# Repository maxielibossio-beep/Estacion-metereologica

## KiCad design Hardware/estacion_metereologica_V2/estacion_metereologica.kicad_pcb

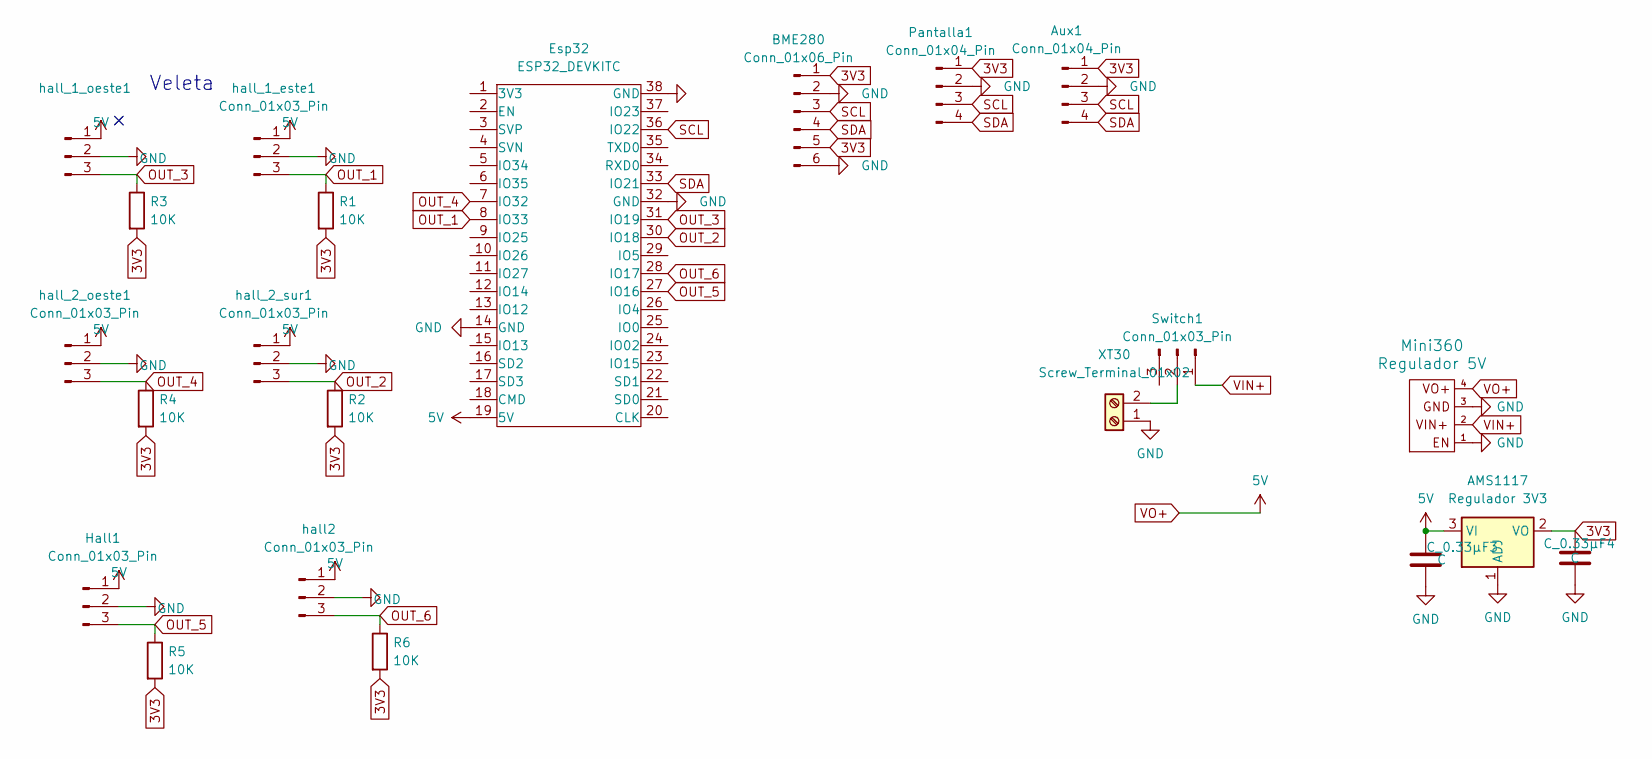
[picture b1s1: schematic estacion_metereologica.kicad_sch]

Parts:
AMS1117: Regulador 3V3; SOT-223-3_TabPin2
Aux1: Conn_01x04_Pin; JST_EH_B4B-EH-A_1x04_P2.50mm_Vertical
BME280: Conn_01x06_Pin; PinHeader_1x06_P2.54mm_Vertical
C_0.33µF3, C_0.33µF4: C; C_0805_2012Metric
Esp32: ESP32_DEVKITC; ESP32-DevKitC
Hall1: Conn_01x03_Pin; JST_XH_B3B-XH-A_1x03_P2.50mm_Vertical
Mini360: Regulador 5V; Mini360
Pantalla1: Conn_01x04_Pin; JST_EH_B4B-EH-A_1x04_P2.50mm_Vertical
R1, R2, R3, R4, R5, R6: 10K; R_0805_2012Metric_Pad1.20x1.40mm_HandSolder
Switch1: Conn_01x03_Pin; JST_PH_B3B-PH-K_1x03_P2.00mm_Vertical
XT30: Screw_Terminal_01x02; AMASS_XT30U-F_1x02_P5.0mm_Vertical
hall2: Conn_01x03_Pin; JST_XH_B3B-XH-A_1x03_P2.50mm_Vertical
hall_1_este1, hall_1_oeste1, hall_2_oeste1, hall_2_sur1: Conn_01x03_Pin; JST_XH_B3B-XH-A_1x03_P2.50mm_Vertical

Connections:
3V3: AMS1117.2 (VO), Aux1.1, BME280.1, BME280.5, C_0.33µF4.1, Pantalla1.1, R1.2, R2.2, R3.2, R4.2, R5.2, R6.2
GND: AMS1117.1 (ADJ), Aux1.2, BME280.2, BME280.6, C_0.33µF3.2, C_0.33µF4.2, Esp32.14 (GND), Esp32.32 (GND), Esp32.38 (GND), Hall1.2, Mini360.1, Mini360.3, Pantalla1.2, XT30.1, hall2.2, hall_1_este1.2, hall_1_oeste1.2, hall_2_oeste1.2, hall_2_sur1.2
unnamed: Switch1.2, XT30.2
OUT_1: Esp32.8 (IO33), R1.1, hall_1_este1.3
OUT_2: Esp32.30 (IO18), R2.1, hall_2_sur1.3
OUT_3: Esp32.31 (IO19), R3.1, hall_1_oeste1.3
OUT_4: Esp32.7 (IO32), R4.1, hall_2_oeste1.3
OUT_5: Esp32.27 (IO16), Hall1.3, R5.1
OUT_6: Esp32.28 (IO17), R6.1, hall2.3
SCL: Aux1.3, BME280.3, Esp32.36 (IO22), Pantalla1.3
SDA: Aux1.4, BME280.4, Esp32.33 (IO21), Pantalla1.4
VIN+: Mini360.2, Switch1.1
VO+: AMS1117.3 (VI), C_0.33µF3.1, Esp32.19 (5V), Hall1.1, Mini360.4, hall2.1, hall_1_este1.1, hall_1_oeste1.1, hall_2_oeste1.1, hall_2_sur1.1

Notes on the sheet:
Veleta

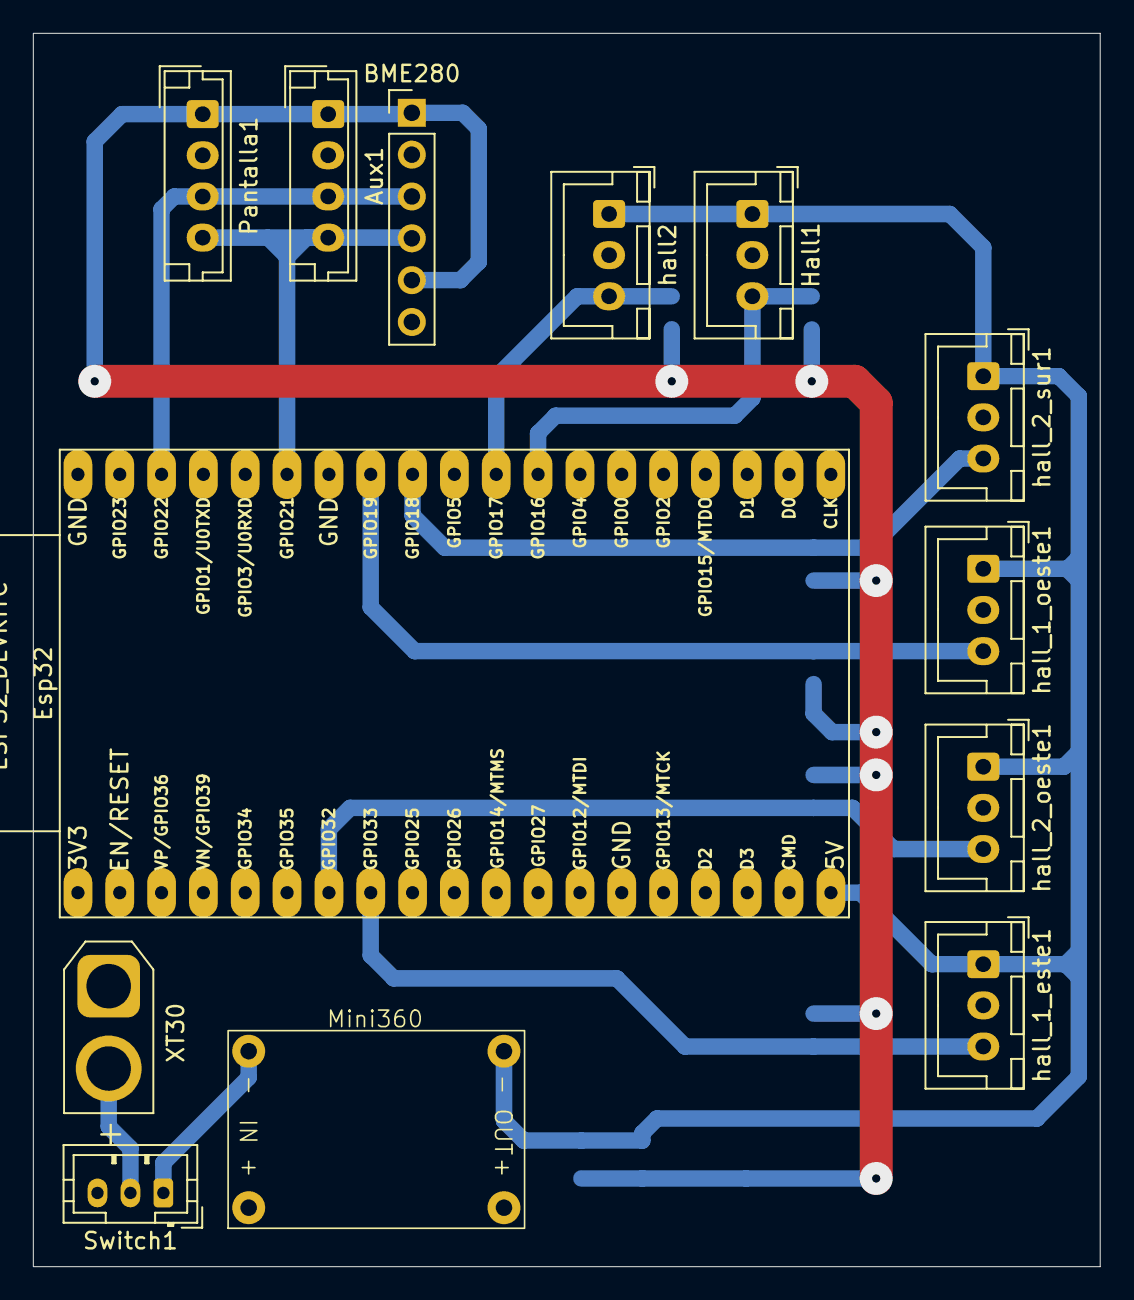
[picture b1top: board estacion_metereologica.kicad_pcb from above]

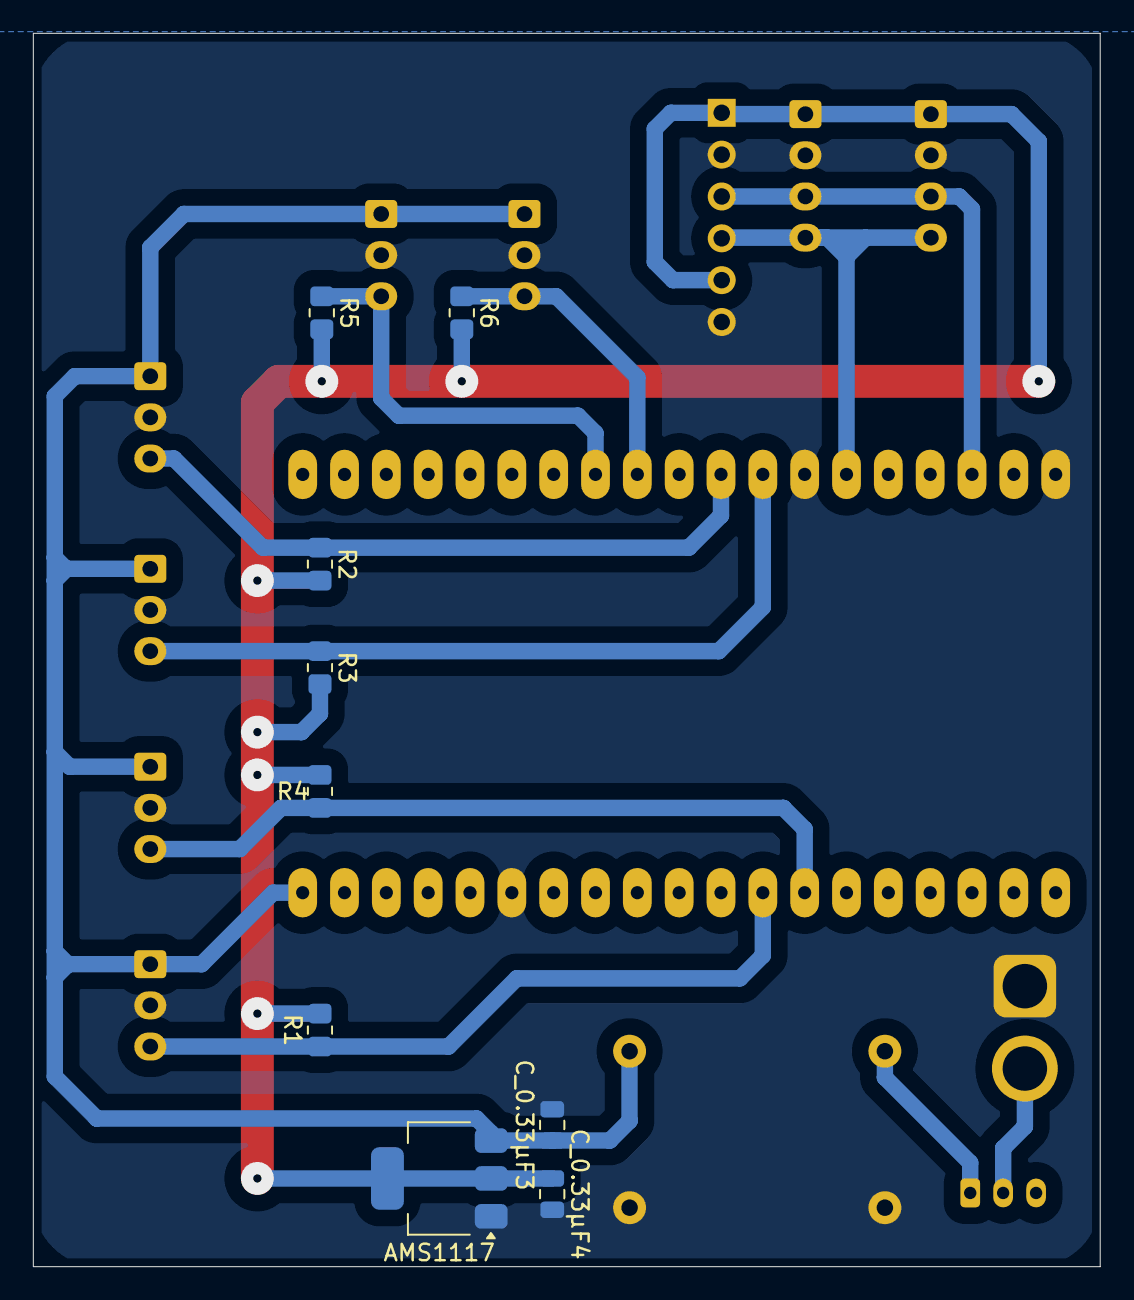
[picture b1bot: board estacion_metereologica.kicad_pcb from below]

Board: 2 copper layers, 64.8 x 74.9 mm, 22 parts (9 on the bottom side), 13 nets.

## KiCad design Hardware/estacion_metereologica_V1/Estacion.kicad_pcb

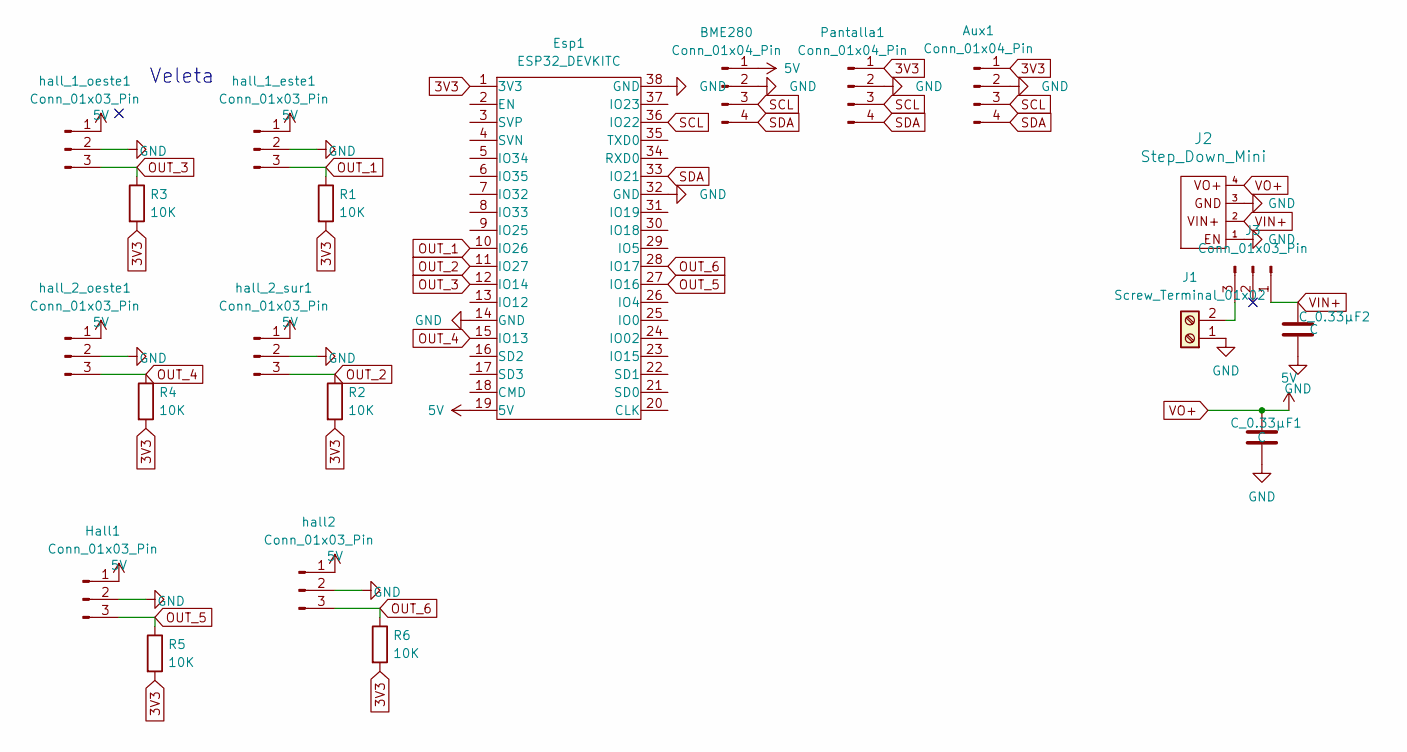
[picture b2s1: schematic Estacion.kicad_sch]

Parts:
Aux1: Conn_01x04_Pin; JST_PH_B4B-PH-K_1x04_P2.00mm_Vertical
BME280: Conn_01x04_Pin; JST_PH_B4B-PH-K_1x04_P2.00mm_Vertical
C_0.33µF1, C_0.33µF2: C; C_0805_2012Metric
Esp1: ESP32_DEVKITC; ESP32-DevKitC
Hall1: Conn_01x03_Pin; JST_PH_B3B-PH-K_1x03_P2.00mm_Vertical
J1: Screw_Terminal_01x02; AMASS_XT30U-F_1x02_P5.0mm_Vertical
J2: Step_Down_Mini; Mini360
J3: Conn_01x03_Pin; JST_PH_B3B-PH-K_1x03_P2.00mm_Vertical
Pantalla1: Conn_01x04_Pin; JST_PH_B4B-PH-K_1x04_P2.00mm_Vertical
R1, R2, R3, R4, R5, R6: 10K; R_0805_2012Metric_Pad1.20x1.40mm_HandSolder
hall2: Conn_01x03_Pin; JST_PH_B3B-PH-K_1x03_P2.00mm_Vertical
hall_1_este1, hall_1_oeste1, hall_2_oeste1, hall_2_sur1: Conn_01x03_Pin; JST_PH_B3B-PH-K_1x03_P2.00mm_Vertical

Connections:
3V3: Aux1.1, Esp1.1 (3V3), Pantalla1.1, R1.2, R2.2, R3.2, R4.2, R5.2, R6.2
GND: Aux1.2, BME280.2, C_0.33µF1.2, C_0.33µF2.2, Esp1.14 (GND), Esp1.32 (GND), Esp1.38 (GND), Hall1.2, J1.1, J2.1, J2.3, Pantalla1.2, hall2.2, hall_1_este1.2, hall_1_oeste1.2, hall_2_oeste1.2, hall_2_sur1.2
unnamed: J1.2, J3.3
OUT_1: Esp1.10 (IO26), R1.1, hall_1_este1.3
OUT_2: Esp1.11 (IO27), R2.1, hall_2_sur1.3
OUT_3: Esp1.12 (IO14), R3.1, hall_1_oeste1.3
OUT_4: Esp1.15 (IO13), R4.1, hall_2_oeste1.3
OUT_5: Esp1.27 (IO16), Hall1.3, R5.1
OUT_6: Esp1.28 (IO17), R6.1, hall2.3
SCL: Aux1.3, BME280.3, Esp1.36 (IO22), Pantalla1.3
SDA: Aux1.4, BME280.4, Esp1.33 (IO21), Pantalla1.4
VIN+: C_0.33µF2.1, J2.2, J3.1
VO+: BME280.1, C_0.33µF1.1, Esp1.19 (5V), Hall1.1, J2.4, hall2.1, hall_1_este1.1, hall_1_oeste1.1, hall_2_oeste1.1, hall_2_sur1.1

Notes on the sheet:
Veleta

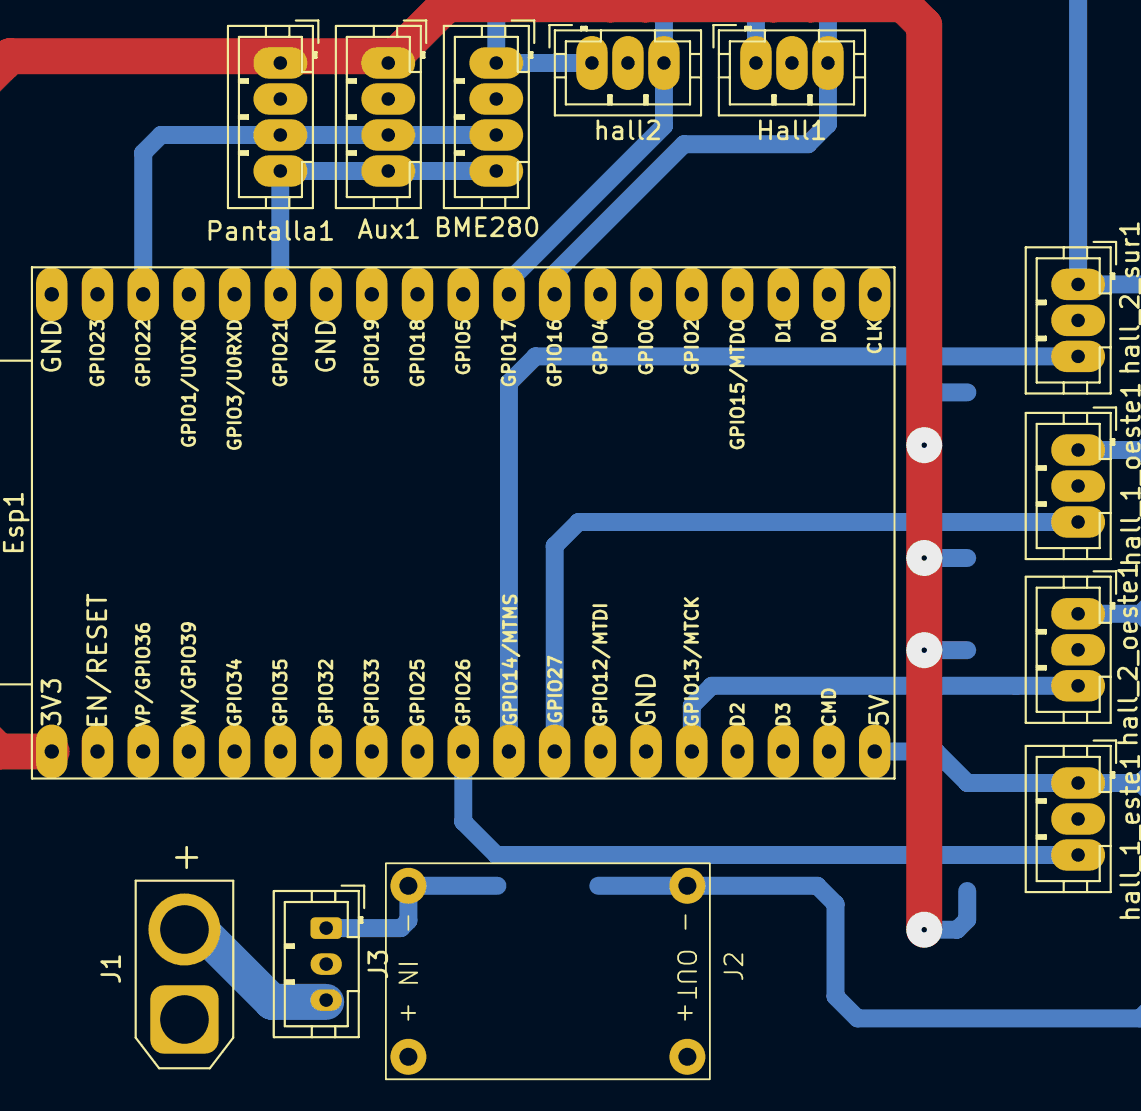
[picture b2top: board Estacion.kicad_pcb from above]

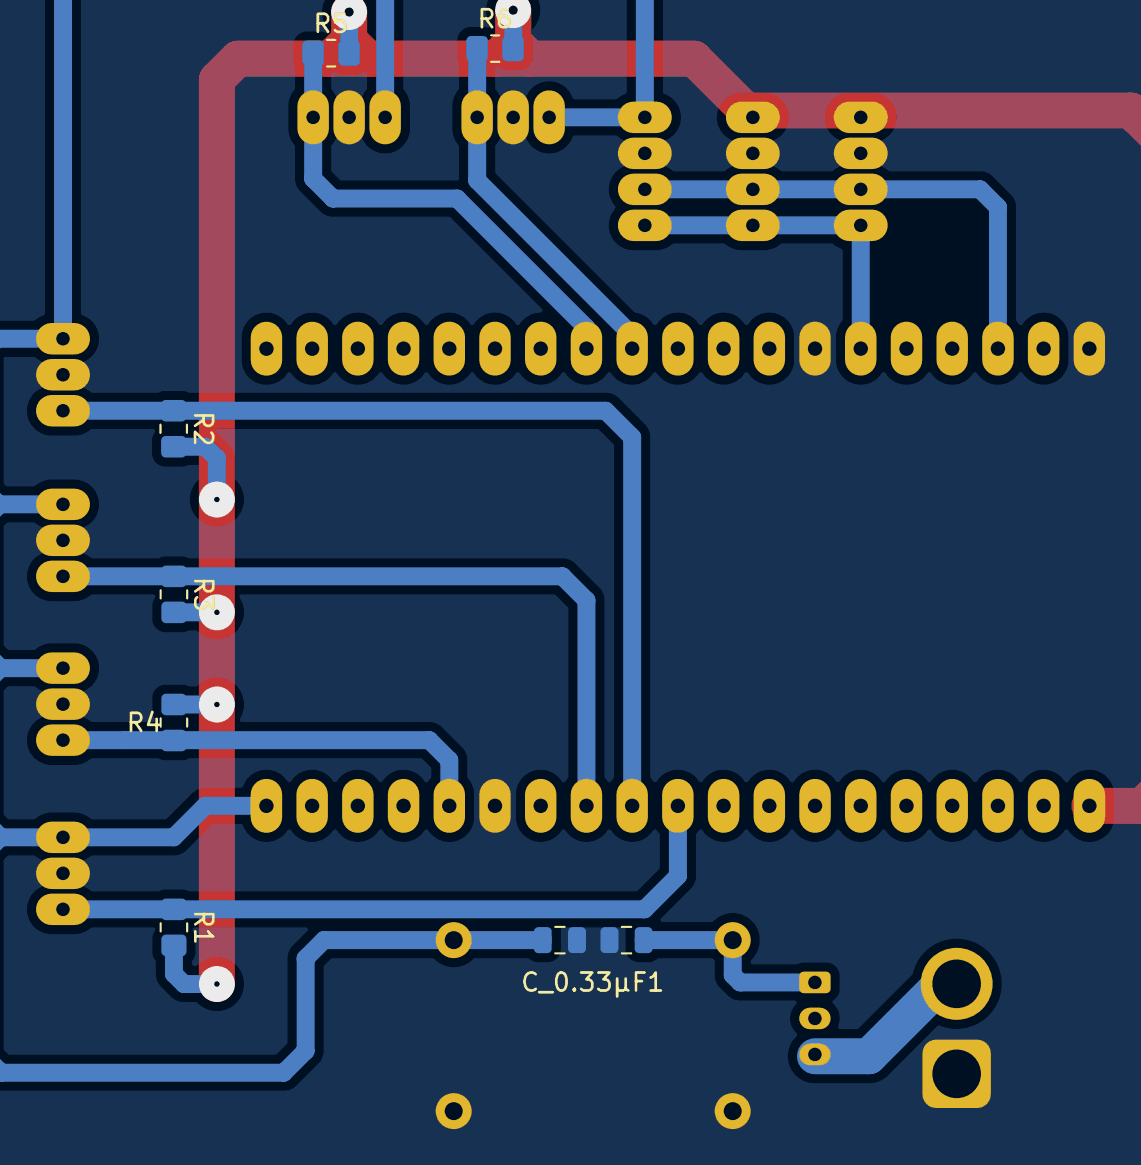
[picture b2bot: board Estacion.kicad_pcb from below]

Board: 2 copper layers, 21 parts (8 on the bottom side), 13 nets.
